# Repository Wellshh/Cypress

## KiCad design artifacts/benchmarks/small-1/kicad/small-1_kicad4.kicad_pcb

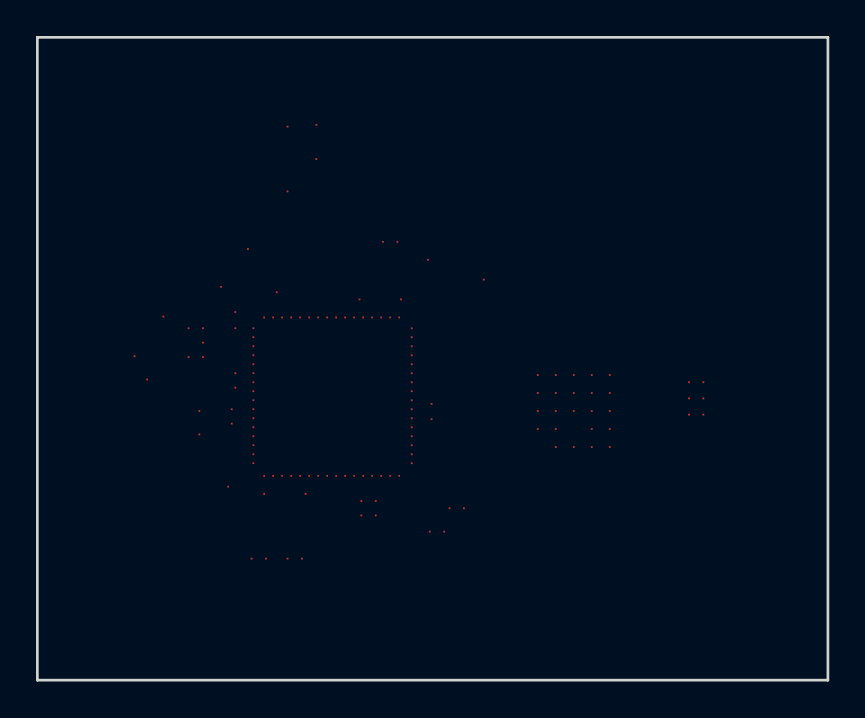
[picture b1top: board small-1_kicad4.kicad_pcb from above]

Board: 2 copper layers, 43.9 x 35.7 mm, 57 parts (0 on the bottom side), 36 nets, no tracks yet.

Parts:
C0: C0; 195-3953-000
C1: C1; 195-2655-000
C2: C2; 195-0150-000
C3: C3; 195-0339-000
C4: C4; 035-0020-000
C5: C5; 035-0020-000
C6: C6; 195-0167-000
C7: C7; 195-0167-000
C8: C8; 195-0167-000
C9: C9; 195-0167-000
C10: C10; 195-0004-000
C11: C11; 195-0004-000
C12: C12; 195-0004-000
C13: C13; 195-0004-000
C14: C14; 195-0004-000
C15: C15; 195-0004-000
C16: C16; 195-0004-000
C17: C17; 195-3953-000
C18: C18; 195-3953-000
C19: C19; 195-3953-000
C20: C20; 195-3953-000
C21: C21; 195-3953-000
C22: C22; 032-0863-000
C23: C23; 032-0793-000
C24: C24; 032-0793-000
C25: C25; 032-1794-000
C26: C26; 032-0793-000
C27: C27; 032-0793-000
C28: C28; 032-0793-000
C29: C29; 032-0793-000
C30: C30; 032-0793-000
C31: C31; 032-0793-000
C32: C32; 032-0793-000
C33: C33; 032-0793-000
C34: C34; 032-0793-000
C35: C35; 032-0793-000
C36: C36; 032-0793-000
C37: C37; 032-0793-000
C38: C38; 195-2655-000
C39: C39; 195-3953-000
C40: C40; 195-3953-000
C41: C41; 195-3953-000
C42: C42; 195-0004-000
C43: C43; 195-3953-000
C44: C44; 085-0357-000
C45: C45; 115-3708-000
C46: C46; 100-0275-000
C47: C47; 170-0572-500
C48: C48; 032-1812-000
C49: C49; 032-2145-000
C50: C50; 032-2145-000
C51: C51; 032-0055-000
C52: C52; 032-0816-000
C53: C53; 032-0816-000
C54: C54; 032-0816-000
C55: C55; 032-0816-000
C56: C56; 032-0816-000

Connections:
NET_0: C27.1, C29.1, C34.1, C37.1, C45.11, C45.32, C45.38, C45.42, C45.59, C50.1, C52.1
NET_15: C28.1, C30.1, C33.1, C35.1, C45.39, C45.47, C45.56, C49.1, C53.1
NET_79: C25.1, C26.1, C31.1, C32.1, C36.1, C45.10, C45.27, C45.41, C45.51, C45.64, C46.2, C51.1, C54.1, C55.1
NET_80: C0.1, C2.1, C10.1, C12.1, C14.1, C16.1, C17.1, C18.1, C19.1, C21.1, C22.1, C40.1, C41.1, C42.2, C43.1, C46.1, C47.B4, C56.1
NET_908: C0.2, C47.A4
NET_2870: C42.1, C45.4
NET_3021: C40.2, C45.31
NET_3022: C41.2, C45.30
NET_3220: C24.1, C45.20
NET_3222: C23.1, C45.21
NET_3333: C45.37, C48.2
NET_3334: C45.40, C48.1
NET_3335: C19.2, C45.61
NET_3337: C38.2, C45.46
NET_3338: C5.1, C38.1, C44.3
NET_3339: C1.2, C45.45
NET_3340: C1.1, C4.1, C44.1
NET_3355: C11.1, C45.2
NET_3356: C13.1, C45.3
NET_3357: C16.2, C45.6
NET_3358: C14.2, C45.5
NET_3359: C12.2, C45.9
NET_3360: C10.2, C45.8
NET_3361: C15.1, C45.7
NET_3434: C8.2, C47.D2
NET_3436: C6.2, C45.13
NET_3438: C7.2, C45.15
NET_3441: C9.2, C45.12
NET_3482: C18.2, C47.D4
NET_3483: C17.2, C47.C4
NET_5155: C2.2, C45.16
NET_5156: C21.2, C45.28
NET_5157: C20.1, C45.17
NET_5160: C39.1, C45.1
NET_5162: C3.2, C45.48
NET_5163: C43.2, C45.35

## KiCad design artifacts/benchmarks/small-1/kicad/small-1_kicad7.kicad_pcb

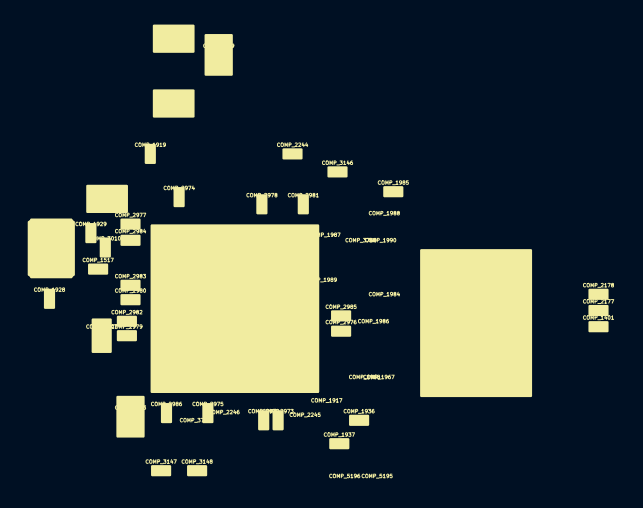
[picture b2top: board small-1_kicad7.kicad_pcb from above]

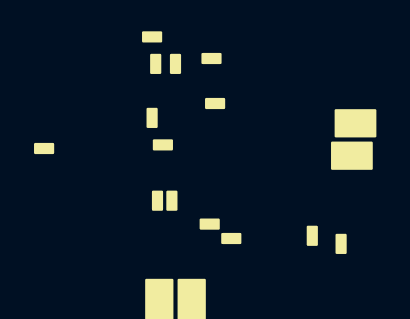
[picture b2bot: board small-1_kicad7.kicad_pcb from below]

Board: 2 copper layers, 57 parts (18 on the bottom side), 36 nets, no tracks yet.

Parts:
COMP_1401: COMP_1401; 195-3953-000
COMP_1517: COMP_1517; 195-2655-000
COMP_1917: COMP_1917; 195-0150-000
COMP_1919: COMP_1919; 195-0339-000
COMP_1928: COMP_1928; 035-0020-000
COMP_1929: COMP_1929; 035-0020-000
COMP_1936: COMP_1936; 195-0167-000
COMP_1937: COMP_1937; 195-0167-000
COMP_1967: COMP_1967; 195-0167-000
COMP_1968: COMP_1968; 195-0167-000
COMP_1984: COMP_1984; 195-0004-000
COMP_1985: COMP_1985; 195-0004-000
COMP_1986: COMP_1986; 195-0004-000
COMP_1987: COMP_1987; 195-0004-000
COMP_1988: COMP_1988; 195-0004-000
COMP_1989: COMP_1989; 195-0004-000
COMP_1990: COMP_1990; 195-0004-000
COMP_2177: COMP_2177; 195-3953-000
COMP_2178: COMP_2178; 195-3953-000
COMP_2244: COMP_2244; 195-3953-000
COMP_2245: COMP_2245; 195-3953-000
COMP_2246: COMP_2246; 195-3953-000
COMP_2368: COMP_2368; 032-0863-000
COMP_2972: COMP_2972; 032-0793-000
COMP_2973: COMP_2973; 032-0793-000
COMP_2974: COMP_2974; 032-1794-000
COMP_2975: COMP_2975; 032-0793-000
COMP_2976: COMP_2976; 032-0793-000
COMP_2977: COMP_2977; 032-0793-000
COMP_2978: COMP_2978; 032-0793-000
COMP_2979: COMP_2979; 032-0793-000
COMP_2980: COMP_2980; 032-0793-000
COMP_2981: COMP_2981; 032-0793-000
COMP_2982: COMP_2982; 032-0793-000
COMP_2983: COMP_2983; 032-0793-000
COMP_2984: COMP_2984; 032-0793-000
COMP_2985: COMP_2985; 032-0793-000
COMP_2986: COMP_2986; 032-0793-000
COMP_3010: COMP_3010; 195-2655-000
COMP_3146: COMP_3146; 195-3953-000
COMP_3147: COMP_3147; 195-3953-000
COMP_3148: COMP_3148; 195-3953-000
COMP_3760: COMP_3760; 195-0004-000
COMP_3762: COMP_3762; 195-3953-000
COMP_4496: COMP_4496; 085-0357-000
COMP_4510: COMP_4510; 115-3708-000
COMP_4549: COMP_4549; 100-0275-000
COMP_4702: COMP_4702; 170-0572-500
COMP_4807: COMP_4807; 032-1812-000
COMP_5186: COMP_5186; 032-2145-000
COMP_5191: COMP_5191; 032-2145-000
COMP_5192: COMP_5192; 032-0055-000
COMP_5193: COMP_5193; 032-0816-000
COMP_5194: COMP_5194; 032-0816-000
COMP_5195: COMP_5195; 032-0816-000
COMP_5196: COMP_5196; 032-0816-000
COMP_5197: COMP_5197; 032-0816-000

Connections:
NET_0: COMP_2976.1, COMP_2978.1, COMP_2983.1, COMP_2986.1, COMP_4510.11, COMP_4510.32, COMP_4510.38, COMP_4510.42, COMP_4510.59, COMP_5191.1, COMP_5193.1
NET_15: COMP_2977.1, COMP_2979.1, COMP_2982.1, COMP_2984.1, COMP_4510.39, COMP_4510.47, COMP_4510.56, COMP_5186.1, COMP_5194.1
NET_79: COMP_2974.1, COMP_2975.1, COMP_2980.1, COMP_2981.1, COMP_2985.1, COMP_4510.10, COMP_4510.27, COMP_4510.41, COMP_4510.51, COMP_4510.64, COMP_4549.2, COMP_5192.1, COMP_5195.1, COMP_5196.1
NET_80: COMP_1401.1, COMP_1917.1, COMP_1984.1, COMP_1986.1, COMP_1988.1, COMP_1990.1, COMP_2177.1, COMP_2178.1, COMP_2244.1, COMP_2246.1, COMP_2368.1, COMP_3147.1, COMP_3148.1, COMP_3760.2, COMP_3762.1, COMP_4549.1, COMP_4702.B4, COMP_5197.1
NET_908: COMP_1401.2, COMP_4702.A4
NET_2870: COMP_3760.1, COMP_4510.4
NET_3021: COMP_3147.2, COMP_4510.31
NET_3022: COMP_3148.2, COMP_4510.30
NET_3220: COMP_2973.1, COMP_4510.20
NET_3222: COMP_2972.1, COMP_4510.21
NET_3333: COMP_4510.37, COMP_4807.2
NET_3334: COMP_4510.40, COMP_4807.1
NET_3335: COMP_2244.2, COMP_4510.61
NET_3337: COMP_3010.2, COMP_4510.46
NET_3338: COMP_1929.1, COMP_3010.1, COMP_4496.3
NET_3339: COMP_1517.2, COMP_4510.45
NET_3340: COMP_1517.1, COMP_1928.1, COMP_4496.1
NET_3355: COMP_1985.1, COMP_4510.2
NET_3356: COMP_1987.1, COMP_4510.3
NET_3357: COMP_1990.2, COMP_4510.6
NET_3358: COMP_1988.2, COMP_4510.5
NET_3359: COMP_1986.2, COMP_4510.9
NET_3360: COMP_1984.2, COMP_4510.8
NET_3361: COMP_1989.1, COMP_4510.7
NET_3434: COMP_1967.2, COMP_4702.D2
NET_3436: COMP_1936.2, COMP_4510.13
NET_3438: COMP_1937.2, COMP_4510.15
NET_3441: COMP_1968.2, COMP_4510.12
NET_3482: COMP_2178.2, COMP_4702.D4
NET_3483: COMP_2177.2, COMP_4702.C4
NET_5155: COMP_1917.2, COMP_4510.16
NET_5156: COMP_2246.2, COMP_4510.28
NET_5157: COMP_2245.1, COMP_4510.17
NET_5160: COMP_3146.1, COMP_4510.1
NET_5162: COMP_1919.2, COMP_4510.48
NET_5163: COMP_3762.2, COMP_4510.35

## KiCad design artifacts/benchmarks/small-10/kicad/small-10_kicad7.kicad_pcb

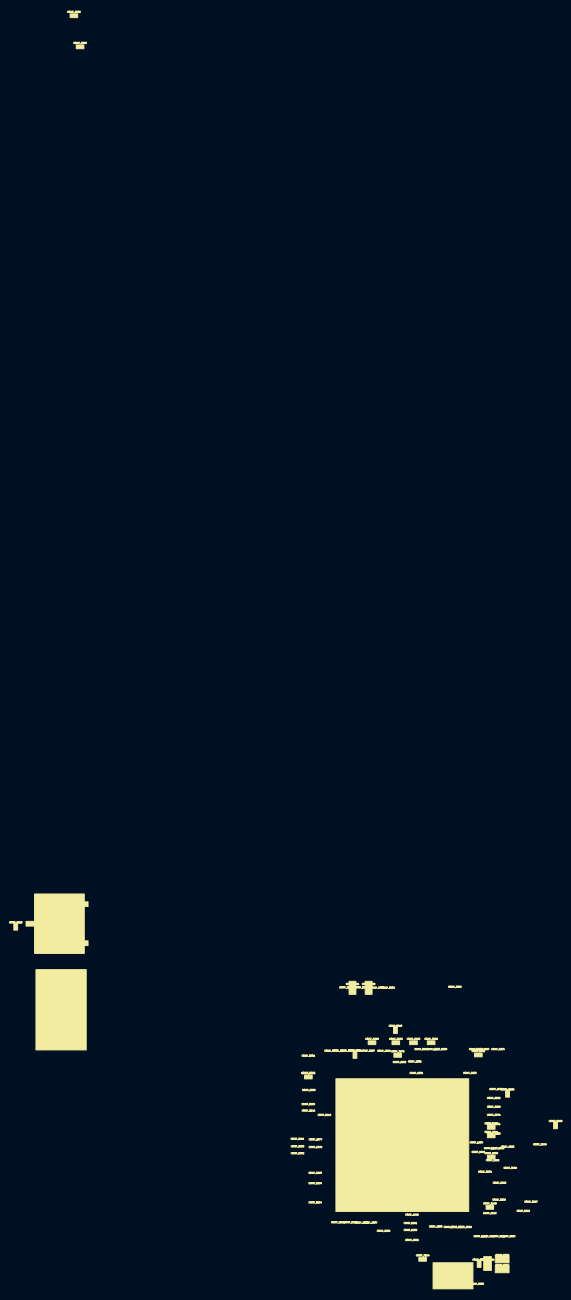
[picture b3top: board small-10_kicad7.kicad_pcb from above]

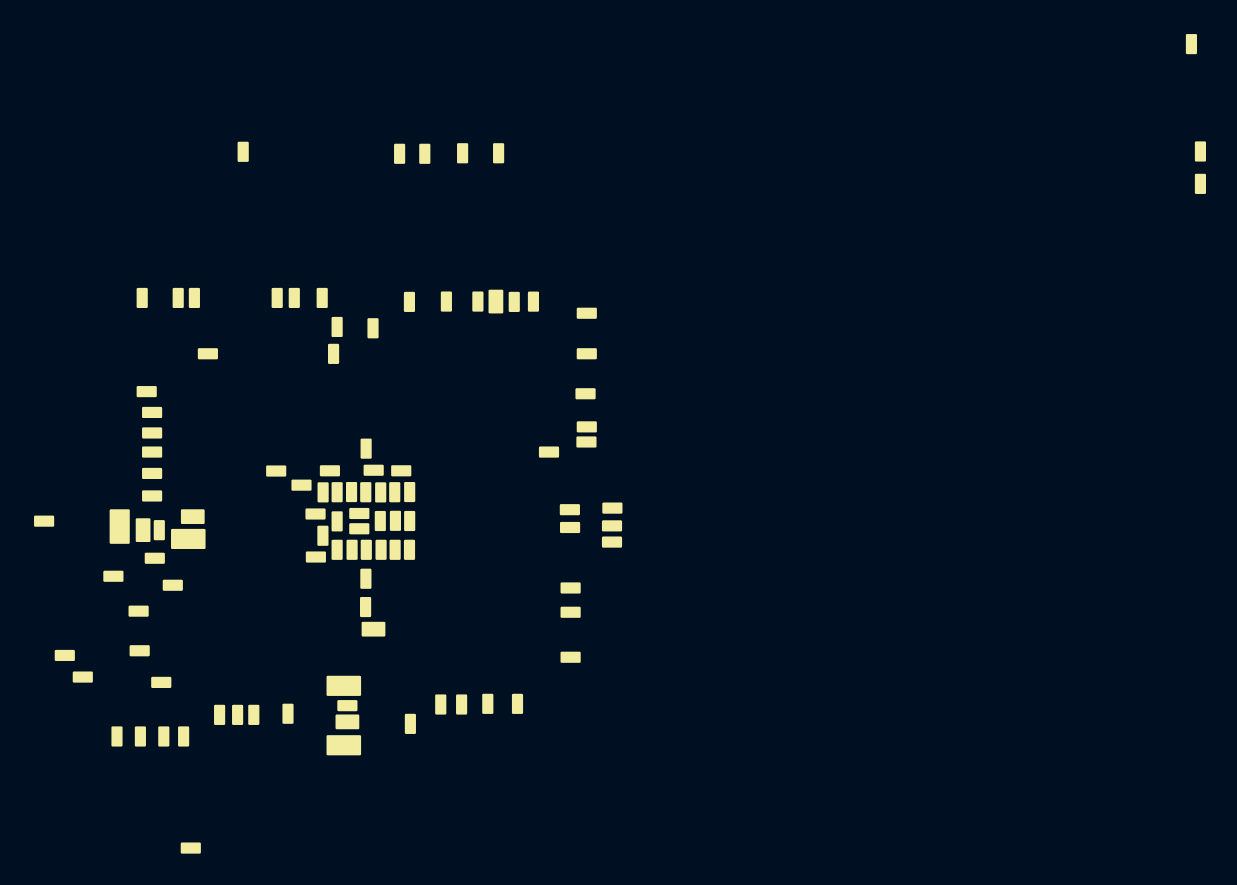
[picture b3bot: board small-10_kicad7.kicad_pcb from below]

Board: 2 copper layers, 136 parts (107 on the bottom side), 94 nets, no tracks yet.

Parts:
COMP_1235: COMP_1235; 080-1776-000
COMP_1236: COMP_1236; 086-0351-000
COMP_1383: COMP_1383; 080-1982-000
COMP_1521: COMP_1521; 092-0256-000
COMP_1522: COMP_1522; 092-0256-000
COMP_1545: COMP_1545; 100-0274-000
COMP_1546: COMP_1546; 100-0274-000
COMP_1547: COMP_1547; 100-0269-000
COMP_1830: COMP_1830; 032-1563-000
COMP_1831: COMP_1831; 032-1641-000
COMP_1832: COMP_1832; 032-1563-000
COMP_1833: COMP_1833; 032-1563-000
COMP_1834: COMP_1834; 032-1641-000
COMP_2022: COMP_2022; 032-0253-000
COMP_2023: COMP_2023; 032-0253-000
COMP_2024: COMP_2024; 039-0135-000
COMP_2025: COMP_2025; 039-0135-000
COMP_2209: COMP_2209; 195-0167-000
COMP_2210: COMP_2210; 195-0167-000
COMP_2211: COMP_2211; 195-0167-000
COMP_2310: COMP_2310; 032-0863-000
COMP_2311: COMP_2311; 032-0863-000
COMP_2312: COMP_2312; 032-0863-000
COMP_2313: COMP_2313; 032-0863-000
COMP_2314: COMP_2314; 032-0863-000
COMP_2315: COMP_2315; 032-0863-000
COMP_2316: COMP_2316; 032-0863-000
COMP_2317: COMP_2317; 032-0863-000
COMP_2318: COMP_2318; 032-0863-000
COMP_2319: COMP_2319; 032-0863-000
COMP_2320: COMP_2320; 032-0863-000
COMP_2321: COMP_2321; 032-0863-000
COMP_2322: COMP_2322; 032-0863-000
COMP_2330: COMP_2330; 195-2655-000
COMP_2331: COMP_2331; 195-2655-000
COMP_2332: COMP_2332; 195-2655-000
COMP_2333: COMP_2333; 195-2655-000
COMP_2334: COMP_2334; 195-2655-000
COMP_2335: COMP_2335; 195-2655-000
COMP_2336: COMP_2336; 195-0167-000
COMP_2337: COMP_2337; 195-0167-000
COMP_2350: COMP_2350; 195-2655-000
COMP_2352: COMP_2352; 195-2655-000
COMP_2356: COMP_2356; 195-2655-000
COMP_2358: COMP_2358; 195-2655-000
COMP_2377: COMP_2377; 195-0167-000
COMP_2378: COMP_2378; 195-0167-000
COMP_2379: COMP_2379; 195-0167-000
COMP_2990: COMP_2990; 195-3953-000
COMP_2991: COMP_2991; 195-3953-000
COMP_2999: COMP_2999; 195-3953-000
COMP_3074: COMP_3074; 195-2655-000
COMP_3075: COMP_3075; 195-2655-000
COMP_3099: COMP_3099; 195-0167-000
COMP_3112: COMP_3112; 195-3953-000
COMP_3113: COMP_3113; 195-3953-000
COMP_3226: COMP_3226; 195-3953-000
COMP_3227: COMP_3227; 195-0128-000
COMP_3228: COMP_3228; 195-3953-000
COMP_3229: COMP_3229; 195-0167-000
COMP_3230: COMP_3230; 195-3953-000
COMP_3231: COMP_3231; 195-0167-000
COMP_3232: COMP_3232; 195-2655-000
COMP_3233: COMP_3233; 195-0167-000
COMP_3234: COMP_3234; 195-0167-000
COMP_3235: COMP_3235; 195-0167-000
COMP_3236: COMP_3236; 195-2655-000
COMP_3237: COMP_3237; 195-0128-000
COMP_3238: COMP_3238; 195-0128-000
COMP_3239: COMP_3239; 195-2655-000
COMP_3240: COMP_3240; 195-2655-000
COMP_3241: COMP_3241; 195-2655-000
COMP_3242: COMP_3242; 195-0252-000
COMP_3243: COMP_3243; 195-0252-000
COMP_3244: COMP_3244; 195-3953-000
COMP_3245: COMP_3245; 195-0167-000
COMP_3246: COMP_3246; 195-0003-000
COMP_3247: COMP_3247; 195-0252-000
COMP_3248: COMP_3248; 195-2655-000
COMP_3249: COMP_3249; 195-0252-000
COMP_3250: COMP_3250; 195-0252-000
COMP_3251: COMP_3251; 195-0005-000
COMP_3252: COMP_3252; 195-3953-000
COMP_3253: COMP_3253; 195-0167-000
COMP_3254: COMP_3254; 195-3953-000
COMP_3255: COMP_3255; 195-0003-000
COMP_3256: COMP_3256; 195-0252-000
COMP_3257: COMP_3257; 195-3953-000
COMP_3258: COMP_3258; 032-0863-000
COMP_3259: COMP_3259; 032-0863-000
COMP_3260: COMP_3260; 032-0863-000
COMP_3261: COMP_3261; 032-0863-000
COMP_3262: COMP_3262; 032-0863-000
COMP_3263: COMP_3263; 032-0863-000
COMP_3264: COMP_3264; 195-3953-000
COMP_3265: COMP_3265; 195-3953-000
COMP_3266: COMP_3266; 195-0167-000
COMP_3267: COMP_3267; 195-0167-000
COMP_3268: COMP_3268; 195-0167-000
COMP_3269: COMP_3269; 195-0252-000
COMP_3270: COMP_3270; 195-3953-000
COMP_3271: COMP_3271; 032-0863-000
COMP_3272: COMP_3272; 032-0863-000
COMP_3273: COMP_3273; 032-0863-000
COMP_3274: COMP_3274; 032-0863-000
COMP_3275: COMP_3275; 032-0863-000
COMP_3276: COMP_3276; 032-0863-000
COMP_3277: COMP_3277; 032-0863-000
COMP_3278: COMP_3278; 032-0863-000
COMP_3279: COMP_3279; 032-0863-000
COMP_3280: COMP_3280; 195-3953-000
COMP_3281: COMP_3281; 032-0863-000
COMP_3282: COMP_3282; 195-3953-000
COMP_3283: COMP_3283; 195-2655-000
COMP_3284: COMP_3284; 195-2655-000
COMP_3285: COMP_3285; 195-2655-000
COMP_3286: COMP_3286; 032-0863-000
COMP_3287: COMP_3287; 195-0167-000
COMP_3288: COMP_3288; 195-0167-000
COMP_3289: COMP_3289; 195-3953-000
COMP_3290: COMP_3290; 195-0167-000
COMP_3291: COMP_3291; 195-2655-000
COMP_3292: COMP_3292; 195-0167-000
COMP_3293: COMP_3293; 195-3953-000
COMP_3294: COMP_3294; 195-0167-000
COMP_3296: COMP_3296; 195-0167-000
COMP_3297: COMP_3297; 032-0863-000
COMP_3298: COMP_3298; 195-0167-000
COMP_3299: COMP_3299; 195-2655-000
COMP_3301: COMP_3301; 195-0167-000
COMP_3302: COMP_3302; 195-3953-000
COMP_3303: COMP_3303; 195-3953-000
COMP_3304: COMP_3304; 195-3953-000
COMP_3305: COMP_3305; 032-0863-000
COMP_3306: COMP_3306; 195-2655-000
COMP_5211: COMP_5211; 115-2974-000

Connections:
NET_0: COMP_1546.2, COMP_1834.1, COMP_3271.1, COMP_3286.1, COMP_5211.J7, COMP_5211.J8
NET_19: COMP_1546.1, COMP_1833.1, COMP_2023.1, COMP_3297.1
NET_20: COMP_1545.2, COMP_1831.1, COMP_2310.1, COMP_2311.1, COMP_2312.1, COMP_2313.1, COMP_2314.1, COMP_2315.1, COMP_2316.1, COMP_2317.1, COMP_2318.1, COMP_2319.1, COMP_2320.1, COMP_2321.1, COMP_2322.1, COMP_3258.1, COMP_3259.1, COMP_3260.1, COMP_3261.1, COMP_3262.1, COMP_3263.1, COMP_3272.1, COMP_3273.1, COMP_3274.1, COMP_3275.1, COMP_3276.1, COMP_3277.1, COMP_3278.1, COMP_3279.1, COMP_5211.H8, COMP_5211.H9, COMP_5211.H10, COMP_5211.H11, COMP_5211.H12, COMP_5211.H13, COMP_5211.J9, COMP_5211.J10, COMP_5211.J11, COMP_5211.J12, COMP_5211.J13, COMP_5211.K8, COMP_5211.K9, COMP_5211.K12, COMP_5211.K13, COMP_5211.L9, COMP_5211.L12, COMP_5211.L13, COMP_5211.M8, COMP_5211.M9, COMP_5211.M10, COMP_5211.M12, COMP_5211.M13, COMP_5211.N8, COMP_5211.N9, COMP_5211.N10, COMP_5211.N11, COMP_5211.N12, COMP_5211.N13
NET_218: COMP_1383.1, COMP_1383.3, COMP_1521.A, COMP_1522.A, COMP_1545.1, COMP_1547.1, COMP_1832.1, COMP_2022.1, COMP_2025.1, COMP_3230.1, COMP_3244.1, COMP_3251.1, COMP_3254.1, COMP_3257.1, COMP_3264.1, COMP_3265.1, COMP_3270.1, COMP_3281.1, COMP_3303.1
NET_466: COMP_3284.2, COMP_5211.U19
NET_468: COMP_3285.1, COMP_5211.W18
NET_470: COMP_3283.2, COMP_5211.T18
NET_472: COMP_3291.2, COMP_5211.U18
NET_707: COMP_3228.1, COMP_5211.A13
NET_717: COMP_3232.1, COMP_5211.P1
NET_720: COMP_2358.1, COMP_5211.U4
NET_728: COMP_3306.2, COMP_5211.F13
NET_731: COMP_2356.2, COMP_5211.G13
NET_743: COMP_3240.2, COMP_5211.B11
NET_746: COMP_3248.2, COMP_5211.N5
NET_1030: COMP_3282.1, COMP_5211.A7
NET_1031: COMP_3293.1, COMP_5211.A8
NET_1032: COMP_3289.1, COMP_5211.A9
NET_1033: COMP_3280.1, COMP_5211.J15
NET_1034: COMP_3302.1, COMP_5211.H14
NET_1035: COMP_3252.1, COMP_5211.Y13
NET_1036: COMP_3304.1, COMP_5211.R1
NET_1037: COMP_2991.1, COMP_5211.H15
NET_1038: COMP_2990.1, COMP_5211.C19
NET_1123: COMP_2352.1, COMP_5211.J4
NET_1125: COMP_2350.1, COMP_5211.J3
NET_1148: COMP_3227.1, COMP_5211.E14
NET_1149: COMP_1383.2, COMP_3226.1, COMP_3227.2
NET_1155: COMP_1235.1, COMP_3254.2, COMP_5211.E15
NET_1156: COMP_1235.3, COMP_3265.2, COMP_5211.D15
NET_1160: COMP_3288.2, COMP_5211.D1
NET_3366: COMP_3239.2, COMP_5211.C3
NET_3368: COMP_3236.2, COMP_5211.C4
NET_3801: COMP_3257.2, COMP_5211.C13
NET_3802: COMP_3264.2, COMP_5211.Y20
NET_3803: COMP_3244.2, COMP_5211.A19
NET_3804: COMP_1830.1, COMP_3251.2, COMP_5211.C17
NET_3805: COMP_3270.2, COMP_5211.D13
NET_3852: COMP_3238.2, COMP_5211.A17
NET_3853: COMP_1522.K, COMP_3238.1
NET_3854: COMP_3237.2, COMP_5211.A18
NET_3855: COMP_1521.K, COMP_3237.1
NET_4565: COMP_2337.1, COMP_5211.W16
NET_4568: COMP_2330.2, COMP_5211.T10
NET_4571: COMP_2334.2, COMP_5211.P16
NET_4573: COMP_2336.2, COMP_5211.P9
NET_4576: COMP_2331.1, COMP_5211.F10
NET_4579: COMP_2335.2, COMP_5211.D11
NET_4586: COMP_3247.2, COMP_5211.T2
NET_4587: COMP_3242.1, COMP_5211.T3
NET_4588: COMP_3243.1, COMP_5211.V1
NET_4589: COMP_3269.1, COMP_5211.V2
NET_4590: COMP_3267.2, COMP_5211.U1
NET_4591: COMP_3256.2, COMP_5211.T1
NET_4592: COMP_3250.2, COMP_5211.U2
NET_4593: COMP_1236.1, COMP_3303.2
NET_4615: COMP_3294.2, COMP_5211.W9
NET_4616: COMP_1236.3, COMP_3294.1
NET_4666: COMP_2211.2, COMP_5211.J2
NET_4668: COMP_2210.2, COMP_5211.J1
NET_4670: COMP_2209.2, COMP_5211.L4
NET_4674: COMP_3287.2, COMP_5211.K2
NET_4676: COMP_3234.2, COMP_5211.K1
NET_4678: COMP_2379.2, COMP_5211.K6
NET_4682: COMP_3268.2, COMP_5211.K4
NET_4694: COMP_3299.2, COMP_5211.K5
NET_4708: COMP_3249.2, COMP_5211.L3
NET_4710: COMP_3253.1, COMP_5211.E19
NET_4712: COMP_3290.1, COMP_5211.D20
NET_4714: COMP_3298.1, COMP_5211.R3
NET_4716: COMP_3235.1, COMP_5211.R4
NET_4718: COMP_2377.1, COMP_5211.J19
NET_4720: COMP_2378.1, COMP_5211.L17
NET_4731: COMP_3292.1, COMP_5211.D6
NET_4733: COMP_3245.2, COMP_5211.Y4
NET_6414: COMP_3296.2, COMP_5211.G5
NET_6416: COMP_3301.1, COMP_5211.G4
NET_6424: COMP_3241.1, COMP_5211.A3
NET_6427: COMP_2333.1, COMP_5211.F7
NET_6430: COMP_3074.1, COMP_5211.G7
NET_6443: COMP_3233.1, COMP_5211.R12
NET_6445: COMP_2332.2, COMP_5211.G12
NET_6448: COMP_3075.2, COMP_5211.F14
NET_6461: COMP_3231.1, COMP_5211.P12
NET_6462: COMP_3229.1, COMP_5211.G3
NET_6465: COMP_3266.2, COMP_5211.Y3
NET_6527: COMP_3255.1, COMP_5211.V3
NET_6530: COMP_3112.1, COMP_5211.F15
NET_6531: COMP_3113.1, COMP_5211.A20
NET_6532: COMP_2999.1, COMP_5211.B20
NET_6576: COMP_3230.2, COMP_5211.A2
NET_6739: COMP_3099.1, COMP_5211.H1
NET_6882: COMP_3246.1, COMP_5211.G19
NET_6946: COMP_1236.4, COMP_1547.2, COMP_2024.1, COMP_3305.1

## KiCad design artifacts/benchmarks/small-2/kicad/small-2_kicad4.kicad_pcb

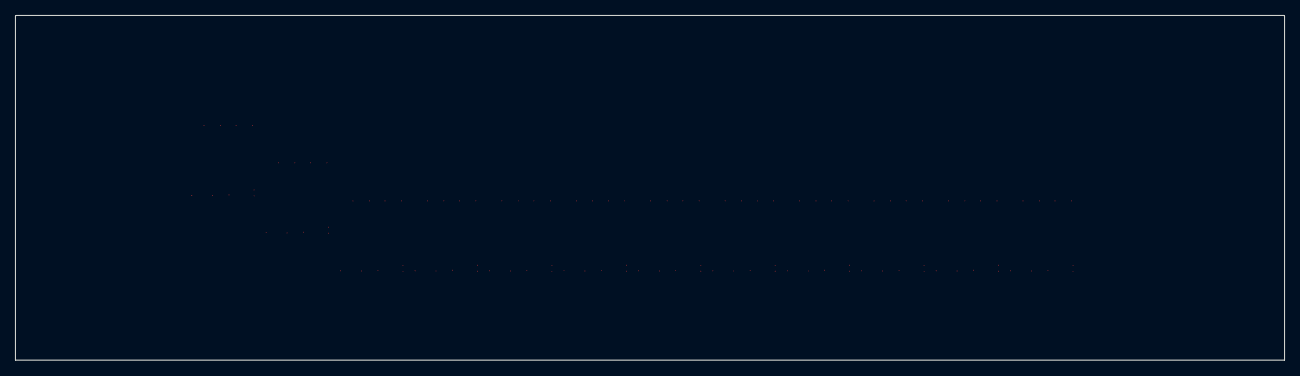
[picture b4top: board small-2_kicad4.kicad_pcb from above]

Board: 2 copper layers, 170.1 x 46.2 mm, 240 parts (0 on the bottom side), 88 nets, no tracks yet.

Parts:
C0: C0; 032-1642-000
C1: C1; 032-1642-000
C2: C2; 032-1642-000
C3: C3; 032-1642-000
C4: C4; 032-1642-000
C5: C5; 032-1642-000
C6: C6; 032-1642-000
C7: C7; 032-1642-000
C8: C8; 032-1642-000
C9: C9; 032-1642-000
C10: C10; 032-1642-000
C11: C11; 032-1642-000
C12: C12; 032-1642-000
C13: C13; 032-1642-000
C14: C14; 032-1642-000
C15: C15; 032-1642-000
C16: C16; 032-1642-000
C17: C17; 032-1642-000
C18: C18; 032-1642-000
C19: C19; 032-1642-000
C20: C20; 032-1642-000
C21: C21; 032-1642-000
C22: C22; 032-1642-000
C23: C23; 032-1642-000
C24: C24; 032-1468-000
C25: C25; 032-1468-000
C26: C26; 032-1468-000
C27: C27; 032-1468-000
C28: C28; 032-1468-000
C29: C29; 032-1468-000
C30: C30; 032-1468-000
C31: C31; 032-1468-000
C32: C32; 032-0863-000
C33: C33; 032-1468-000
C34: C34; 032-1468-000
C35: C35; 032-1468-000
C36: C36; 032-1468-000
C37: C37; 195-3907-000
C38: C38; 195-3907-000
C39: C39; 195-3907-000
C40: C40; 195-3907-000
C41: C41; 195-3907-000
C42: C42; 195-3907-000
C43: C43; 195-3907-000
C44: C44; 195-3907-000
C45: C45; 195-3907-000
C46: C46; 195-3907-000
C47: C47; 195-3907-000
C48: C48; 195-3907-000
C49: C49; 195-3953-000
C50: C50; 195-3953-000
C51: C51; 195-3953-000
C52: C52; 195-3953-000
C53: C53; 195-3953-000
C54: C54; 195-3953-000
C55: C55; 195-3953-000
C56: C56; 195-3953-000
C57: C57; 195-3953-000
C58: C58; 195-3953-000
C59: C59; 195-3953-000
C60: C60; 195-3953-000
C61: C61; 032-0863-000
C62: C62; 032-0863-000
C63: C63; 032-0863-000
C64: C64; 032-0863-000
C65: C65; 032-0863-000
C66: C66; 032-0863-000
C67: C67; 032-0863-000
C68: C68; 032-0863-000
C69: C69; 032-0863-000
C70: C70; 032-0863-000
C71: C71; 032-0863-000
C72: C72; 032-0863-000
C73: C73; 032-0863-000
C74: C74; 032-0863-000
C75: C75; 032-0863-000
C76: C76; 032-0863-000
C77: C77; 032-0863-000
C78: C78; 032-0863-000
C79: C79; 032-0863-000
C80: C80; 032-0863-000
C81: C81; 032-0863-000
C82: C82; 032-0863-000
C83: C83; 032-0863-000
C84: C84; 195-2655-000
C85: C85; 195-2655-000
C86: C86; 195-2655-000
C87: C87; 195-2655-000
C88: C88; 195-2655-000
C89: C89; 195-2655-000
C90: C90; 195-2655-000
C91: C91; 195-2655-000
C92: C92; 195-2655-000
C93: C93; 195-2655-000
C94: C94; 195-2655-000
C95: C95; 195-2655-000
C96: C96; 195-2655-000
C97: C97; 195-2655-000
C98: C98; 195-2655-000
C99: C99; 195-2655-000
C100: C100; 195-2655-000
C101: C101; 195-2655-000
C102: C102; 195-2655-000
C103: C103; 195-2655-000
C104: C104; 195-2655-000
C105: C105; 195-2655-000
C106: C106; 195-2655-000
C107: C107; 195-2655-000
C108: C108; 032-2076-000
C109: C109; 032-2076-000
C110: C110; 032-2076-000
C111: C111; 032-2076-000
C112: C112; 032-2076-000
C113: C113; 032-2076-000
C114: C114; 032-2076-000
C115: C115; 032-2076-000
C116: C116; 032-2076-000
C117: C117; 032-2076-000
C118: C118; 032-2076-000
C119: C119; 032-2076-000
C120: C120; 032-2076-000
C121: C121; 032-2076-000
C122: C122; 032-2076-000
C123: C123; 032-2076-000
C124: C124; 032-2076-000
C125: C125; 032-2076-000
C126: C126; 032-2076-000
C127: C127; 032-2076-000
C128: C128; 032-2076-000
C129: C129; 032-2076-000
C130: C130; 032-2076-000
C131: C131; 032-2076-000
C132: C132; 032-2076-000
C133: C133; 032-2076-000
C134: C134; 032-2076-000
C135: C135; 032-2076-000
C136: C136; 032-2076-000
C137: C137; 032-2076-000
C138: C138; 032-2076-000
C139: C139; 032-2076-000
C140: C140; 032-2076-000
C141: C141; 032-2076-000
C142: C142; 032-2076-000
C143: C143; 032-2076-000
C144: C144; 032-2076-000
C145: C145; 032-2076-000
C146: C146; 032-2076-000
C147: C147; 032-2076-000
C148: C148; 032-2076-000
C149: C149; 032-2076-000
C150: C150; 032-2076-000
C151: C151; 032-2076-000
C152: C152; 032-2076-000
C153: C153; 032-2076-000
C154: C154; 032-2076-000
C155: C155; 032-2076-000
C156: C156; 316-0577-000
C157: C157; 316-0577-000
C158: C158; 316-0577-000
C159: C159; 316-0577-000
C160: C160; 316-0577-000
C161: C161; 316-0577-000
C162: C162; 316-0577-000
C163: C163; 316-0577-000
C164: C164; 316-0577-000
C165: C165; 316-0577-000
C166: C166; 316-0577-000
C167: C167; 316-0577-000
C168: C168; 130-1618-000
C169: C169; 130-1618-000
C170: C170; 130-1618-000
C171: C171; 130-1618-000
C172: C172; 130-1618-000
C173: C173; 130-1618-000
C174: C174; 130-1618-000
C175: C175; 130-1618-000
C176: C176; 130-1618-000
C177: C177; 130-1618-000
C178: C178; 130-1618-000
C179: C179; 130-1618-000
C180: C180; 032-0055-000
C181: C181; 032-0055-000
C182: C182; 032-0055-000
C183: C183; 032-0055-000
C184: C184; 032-0055-000
C185: C185; 032-0055-000
C186: C186; 032-0055-000
C187: C187; 032-0055-000
C188: C188; 032-0055-000
C189: C189; 032-0055-000
C190: C190; 032-0055-000
C191: C191; 032-0055-000
C192: C192; 032-0055-000
C193: C193; 032-0055-000
C194: C194; 032-0055-000
C195: C195; 032-0055-000
C196: C196; 032-0055-000
C197: C197; 032-0055-000
C198: C198; 032-0055-000
C199: C199; 032-0055-000
C200: C200; 032-0055-000
C201: C201; 032-0055-000
C202: C202; 032-0055-000
C203: C203; 032-0055-000
C204: C204; 032-0055-000
C205: C205; 032-0055-000
C206: C206; 032-0055-000
C207: C207; 032-0055-000
C208: C208; 032-0055-000
C209: C209; 032-0055-000
C210: C210; 032-0055-000
C211: C211; 032-0055-000
C212: C212; 032-0055-000
C213: C213; 032-0055-000
C214: C214; 032-0055-000
C215: C215; 032-0055-000
C216: C216; 032-0055-000
C217: C217; 032-0055-000
C218: C218; 032-0055-000
C219: C219; 032-0055-000
C220: C220; 032-0055-000
C221: C221; 032-0055-000
C222: C222; 032-0055-000
C223: C223; 032-0055-000
C224: C224; 032-0055-000
C225: C225; 032-0055-000
C226: C226; 032-0055-000
C227: C227; 032-0055-000
C228: C228; 032-1638-000
C229: C229; 032-1638-000
C230: C230; 032-1638-000
C231: C231; 032-1638-000
C232: C232; 032-1638-000
C233: C233; 032-1638-000
C234: C234; 032-1638-000
C235: C235; 032-1638-000
C236: C236; 032-1638-000
C237: C237; 032-1638-000
C238: C238; 032-1638-000
C239: C239; 032-1638-000

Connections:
NET_10: C32.1, C61.1, C62.1, C63.1, C64.1, C65.1, C66.1, C67.1, C68.1, C69.1, C70.1, C71.1, C72.1, C73.1, C74.1, C75.1, C76.1, C77.1, C78.1, C79.1, C80.1, C81.1, C82.1, C83.1, C108.1, C109.1, C110.1, C111.1, C112.1, C113.1, C114.1, C115.1, C116.1, C117.1, C118.1, C119.1, C120.1, C121.1, C122.1, C123.1, C124.1, C125.1, C126.1, C127.1, C128.1, C129.1, C130.1, C131.1, C132.1, C133.1, C134.1, C135.1, C136.1, C137.1, C138.1, C139.1, C140.1, C141.1, C142.1, C143.1, C144.1, C145.1, C146.1, C147.1, C148.1, C149.1, C150.1, C151.1, C152.1, C153.1, C154.1, C155.1, C156.25, C156.30, C157.25, C157.30, C158.25, C158.30, C159.25, C159.30, C160.25, C160.30, C161.25, C161.30, C162.25, C162.30, C163.25, C163.30, C164.25, C164.30, C165.25, C165.30, C166.25, C166.30, C167.25, C167.30
NET_373: C25.1, C98.2
NET_374: C26.1, C99.2
NET_375: C27.1, C100.2
NET_376: C28.1, C101.2
NET_377: C29.1, C102.2
NET_378: C30.1, C103.2
NET_380: C31.1, C104.2
NET_381: C24.1, C105.2
NET_382: C33.1, C106.2
NET_383: C35.1, C97.2
NET_384: C34.1, C84.2
NET_385: C36.1, C107.2
NET_420: C98.1, C156.33
NET_421: C99.1, C157.33
NET_422: C100.1, C158.33
NET_423: C101.1, C159.33
NET_424: C102.1, C160.33
NET_425: C103.1, C161.33
NET_427: C104.1, C162.33
NET_428: C105.1, C163.33
NET_429: C106.1, C164.33
NET_430: C97.1, C166.33
NET_431: C84.1, C165.33
NET_432: C107.1, C167.33
NET_468: C25.2, C156.32
NET_469: C26.2, C157.32
NET_470: C27.2, C158.32
NET_471: C28.2, C159.32
NET_472: C29.2, C160.32
NET_473: C30.2, C161.32
NET_475: C31.2, C162.32
NET_476: C24.2, C163.32
NET_477: C33.2, C164.32
NET_478: C35.2, C166.32
NET_479: C34.2, C165.32
NET_480: C36.2, C167.32
NET_516: C156.10, C156.11, C156.12, C156.13, C156.14, C156.15, C156.16, C156.17, C156.18, C156.19, C179.1
NET_517: C157.10, C157.11, C157.12, C157.13, C157.14, C157.15, C157.16, C157.17, C157.18, C157.19, C178.1
NET_518: C158.10, C158.11, C158.12, C158.13, C158.14, C158.15, C158.16, C158.17, C158.18, C158.19, C177.1
NET_519: C159.10, C159.11, C159.12, C159.13, C159.14, C159.15, C159.16, C159.17, C159.18, C159.19, C176.1
NET_520: C160.10, C160.11, C160.12, C160.13, C160.14, C160.15, C160.16, C160.17, C160.18, C160.19, C175.1
NET_521: C161.10, C161.11, C161.12, C161.13, C161.14, C161.15, C161.16, C161.17, C161.18, C161.19, C174.1
NET_523: C162.10, C162.11, C162.12, C162.13, C162.14, C162.15, C162.16, C162.17, C162.18, C162.19, C173.1
NET_524: C163.10, C163.11, C163.12, C163.13, C163.14, C163.15, C163.16, C163.17, C163.18, C163.19, C172.1
NET_525: C164.10, C164.11, C164.12, C164.13, C164.14, C164.15, C164.16, C164.17, C164.18, C164.19, C171.1
NET_526: C166.10, C166.11, C166.12, C166.13, C166.14, C166.15, C166.16, C166.17, C166.18, C166.19, C169.1
NET_527: C165.10, C165.11, C165.12, C165.13, C165.14, C165.15, C165.16, C165.17, C165.18, C165.19, C170.1
NET_528: C167.10, C167.11, C167.12, C167.13, C167.14, C167.15, C167.16, C167.17, C167.18, C167.19, C168.1
NET_5240: C49.2, C156.35
NET_5241: C50.2, C157.35
NET_5242: C51.2, C158.35
NET_5243: C52.2, C159.35
NET_5244: C53.2, C160.35
NET_5245: C54.2, C161.35
NET_5247: C55.2, C162.35
NET_5248: C56.2, C163.35
NET_5249: C57.2, C164.35
NET_5250: C59.2, C166.35
NET_5251: C58.2, C165.35
NET_5252: C60.2, C167.35
NET_5288: C85.2, C156.36
NET_5289: C86.2, C157.36
NET_5290: C87.2, C158.36
NET_5291: C88.2, C159.36
NET_5292: C89.2, C160.36
NET_5293: C90.2, C161.36
NET_5295: C91.2, C162.36
NET_5296: C92.2, C163.36
NET_5297: C93.2, C164.36
NET_5298: C95.2, C166.36
NET_5299: C94.2, C165.36
NET_5300: C96.2, C167.36
NET_5336: C11.1, C37.2, C49.1, C156.3
NET_5337: C10.1, C38.2, C50.1, C157.3
NET_5338: C9.1, C39.2, C51.1, C158.3
NET_5339: C8.1, C40.2, C52.1, C159.3
NET_5340: C7.1, C41.2, C53.1, C160.3
NET_5341: C6.1, C42.2, C54.1, C161.3
NET_5343: C5.1, C43.2, C55.1, C162.3
NET_5344: C4.1, C44.2, C56.1, C163.3
NET_5345: C3.1, C45.2, C57.1, C164.3
NET_5346: C1.1, C47.2, C59.1, C166.3
NET_5347: C2.1, C46.2, C58.1, C165.3
NET_5348: C0.1, C48.2, C60.1, C167.3
NET_5522: C85.1, C86.1, C87.1, C88.1, C89.1, C90.1, C91.1, C92.1, C93.1, C94.1, C95.1, C96.1
NET_5566: C168.2, C169.2, C170.2, C171.2, C172.2, C173.2, C174.2, C175.2, C176.2, C177.2, C178.2, C179.2, C180.1, C181.1, C182.1, C183.1, C184.1, C185.1, C186.1, C187.1, C188.1, C189.1, C190.1, C191.1, C192.1, C193.1, C194.1, C195.1, C196.1, C197.1, C198.1, C199.1, C200.1, C201.1, C202.1, C203.1, C204.1, C205.1, C206.1, C207.1, C208.1, C209.1, C210.1, C211.1, C212.1, C213.1, C214.1, C215.1, C216.1, C217.1, C218.1, C219.1, C220.1, C221.1, C222.1, C223.1, C224.1, C225.1, C226.1, C227.1, C228.1, C229.1, C230.1, C231.1, C232.1, C233.1, C234.1, C235.1, C236.1, C237.1, C238.1, C239.1
NET_5567: C12.1, C13.1, C14.1, C15.1, C16.1, C17.1, C18.1, C19.1, C20.1, C21.1, C22.1, C23.1, C37.1, C38.1, C39.1, C40.1, C41.1, C42.1, C43.1, C44.1, C45.1, C46.1, C47.1, C48.1, C156.4, C157.4, C158.4, C159.4, C160.4, C161.4, C162.4, C163.4, C164.4, C165.4, C166.4, C167.4

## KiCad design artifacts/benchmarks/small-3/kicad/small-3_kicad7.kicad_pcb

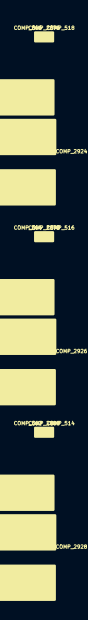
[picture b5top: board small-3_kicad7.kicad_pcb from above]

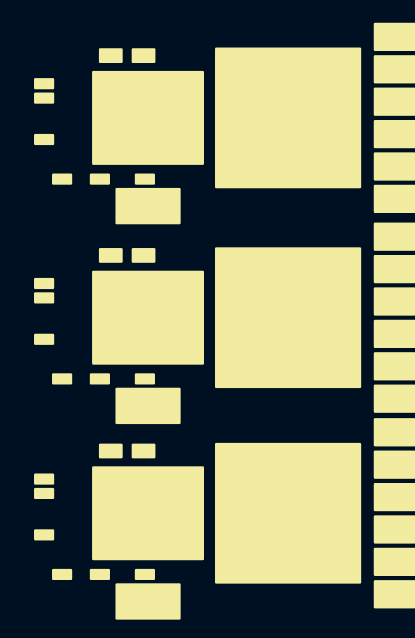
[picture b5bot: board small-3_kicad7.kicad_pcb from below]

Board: 2 copper layers, 63 parts (51 on the bottom side), 26 nets, no tracks yet.

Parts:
COMP_514: COMP_514; 032-1642-000
COMP_516: COMP_516; 032-1642-000
COMP_518: COMP_518; 032-1642-000
COMP_562: COMP_562; 032-1642-000
COMP_564: COMP_564; 032-1642-000
COMP_566: COMP_566; 032-1642-000
COMP_2860: COMP_2860; 032-1468-000
COMP_2862: COMP_2862; 032-1468-000
COMP_2864: COMP_2864; 032-1468-000
COMP_2876: COMP_2876; 195-3907-000
COMP_2878: COMP_2878; 195-3907-000
COMP_2880: COMP_2880; 195-3907-000
COMP_2892: COMP_2892; 195-3953-000
COMP_2894: COMP_2894; 195-3953-000
COMP_2896: COMP_2896; 195-3953-000
COMP_2908: COMP_2908; 032-0863-000
COMP_2910: COMP_2910; 032-0863-000
COMP_2912: COMP_2912; 032-0863-000
COMP_2924: COMP_2924; 032-0863-000
COMP_2926: COMP_2926; 032-0863-000
COMP_2928: COMP_2928; 032-0863-000
COMP_2941: COMP_2941; 195-2655-000
COMP_2943: COMP_2943; 195-2655-000
COMP_2945: COMP_2945; 195-2655-000
COMP_2957: COMP_2957; 195-2655-000
COMP_2959: COMP_2959; 195-2655-000
COMP_2961: COMP_2961; 195-2655-000
COMP_4201: COMP_4201; 032-2076-000
COMP_4203: COMP_4203; 032-2076-000
COMP_4205: COMP_4205; 032-2076-000
COMP_4217: COMP_4217; 032-2076-000
COMP_4219: COMP_4219; 032-2076-000
COMP_4221: COMP_4221; 032-2076-000
COMP_4233: COMP_4233; 032-2076-000
COMP_4235: COMP_4235; 032-2076-000
COMP_4237: COMP_4237; 032-2076-000
COMP_4249: COMP_4249; 032-2076-000
COMP_4251: COMP_4251; 032-2076-000
COMP_4253: COMP_4253; 032-2076-000
COMP_4287: COMP_4287; 130-1566-000
COMP_4289: COMP_4289; 130-1566-000
COMP_4291: COMP_4291; 130-1566-000
COMP_4348: COMP_4348; 316-0577-000
COMP_4350: COMP_4350; 316-0577-000
COMP_4352: COMP_4352; 316-0577-000
COMP_5200: COMP_5200; 032-1721-000
COMP_5202: COMP_5202; 032-1721-000
COMP_5204: COMP_5204; 032-1721-000
COMP_5216: COMP_5216; 032-1721-000
COMP_5218: COMP_5218; 032-1721-000
COMP_5220: COMP_5220; 032-1721-000
COMP_5232: COMP_5232; 032-1721-000
COMP_5234: COMP_5234; 032-1721-000
COMP_5236: COMP_5236; 032-1721-000
COMP_5248: COMP_5248; 032-1721-000
COMP_5250: COMP_5250; 032-1721-000
COMP_5252: COMP_5252; 032-1721-000
COMP_5264: COMP_5264; 032-1721-000
COMP_5266: COMP_5266; 032-1721-000
COMP_5268: COMP_5268; 032-1721-000
COMP_5280: COMP_5280; 032-1721-000
COMP_5282: COMP_5282; 032-1721-000
COMP_5284: COMP_5284; 032-1721-000

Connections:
NET_6: COMP_2908.1, COMP_2910.1, COMP_2912.1, COMP_2924.1, COMP_2926.1, COMP_2928.1, COMP_4201.1, COMP_4203.1, COMP_4205.1, COMP_4217.1, COMP_4219.1, COMP_4221.1, COMP_4233.1, COMP_4235.1, COMP_4237.1, COMP_4249.1, COMP_4251.1, COMP_4253.1, COMP_4348.25, COMP_4348.30, COMP_4350.25, COMP_4350.30, COMP_4352.25, COMP_4352.30
NET_396: COMP_2864.1, COMP_2961.2
NET_397: COMP_2862.1, COMP_2959.2
NET_398: COMP_2860.1, COMP_2957.2
NET_443: COMP_2961.1, COMP_4352.33
NET_444: COMP_2959.1, COMP_4350.33
NET_445: COMP_2957.1, COMP_4348.33
NET_491: COMP_2864.2, COMP_4352.32
NET_492: COMP_2862.2, COMP_4350.32
NET_493: COMP_2860.2, COMP_4348.32
NET_539: COMP_4287.1, COMP_4352.10, COMP_4352.11, COMP_4352.12, COMP_4352.13, COMP_4352.14, COMP_4352.15, COMP_4352.16, COMP_4352.17, COMP_4352.18, COMP_4352.19
NET_540: COMP_4289.1, COMP_4350.10, COMP_4350.11, COMP_4350.12, COMP_4350.13, COMP_4350.14, COMP_4350.15, COMP_4350.16, COMP_4350.17, COMP_4350.18, COMP_4350.19
NET_541: COMP_4291.1, COMP_4348.10, COMP_4348.11, COMP_4348.12, COMP_4348.13, COMP_4348.14, COMP_4348.15, COMP_4348.16, COMP_4348.17, COMP_4348.18, COMP_4348.19
NET_650: COMP_4287.2, COMP_5200.1, COMP_5216.1, COMP_5232.1, COMP_5248.1, COMP_5264.1, COMP_5280.1
NET_2431: COMP_4289.2, COMP_4291.2, COMP_5202.1, COMP_5204.1, COMP_5218.1, COMP_5220.1, COMP_5234.1, COMP_5236.1, COMP_5250.1, COMP_5252.1, COMP_5266.1, COMP_5268.1, COMP_5282.1, COMP_5284.1
NET_5136: COMP_2941.1, COMP_2943.1
NET_5263: COMP_2896.2, COMP_4352.35
NET_5264: COMP_2894.2, COMP_4350.35
NET_5265: COMP_2892.2, COMP_4348.35
NET_5311: COMP_2945.2, COMP_4352.36
NET_5312: COMP_2943.2, COMP_4350.36
NET_5313: COMP_2941.2, COMP_4348.36
NET_5359: COMP_514.1, COMP_2880.2, COMP_2896.1, COMP_4352.3
NET_5360: COMP_516.1, COMP_2878.2, COMP_2894.1, COMP_4350.3
NET_5361: COMP_518.1, COMP_2876.2, COMP_2892.1, COMP_4348.3
NET_5567: COMP_562.1, COMP_564.1, COMP_566.1, COMP_2876.1, COMP_2878.1, COMP_2880.1, COMP_4348.4, COMP_4350.4, COMP_4352.4
